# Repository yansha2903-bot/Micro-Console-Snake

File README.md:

# SnakeOnXIAO 🐍

A pocket-sized, custom-built retro gaming console made from scratch just to play the legendary Snake game!

This repository contains the full hardware design (KiCad schematic and PCB layout) and the custom C++ game engine running on a **Seeed Studio XIAO RP2040** microcontroller.

---

##  Project Structure

* **`PCB/`** — KiCad project files:
* `*.kicad_pro` — KiCad project management file.
* `*.kicad_sch` — Clean electrical schematic with custom net labels.
* `*.kicad_pcb` — Custom PCB routing, component layout, and geometric board shape.
* **`Firmware/`** — Game source code:
* `*codeSnake.ino` — Arduino IDE C++ sketch running the custom Snake game loop.
* * **`Images`** — images of my project.

---

##  Hardware & Architecture

* **Microcontroller:** Seeed Studio XIAO RP2040 (chosen for its tiny form factor and huge performance).
* **Display:** 0.96" I2C OLED display ($128 \times 64$ pixels) powered by the SSD1306 driver.
* **Controls:** 4x 6x6mm tactile buttons arranged as a classic D-Pad layout for fluid movement.
* **Pinout Configuration:**
* **Buttons (D-Pad):** Connected directly to digital pins `D0` (Up), `D1` (Down), `D2` (Left), and `D3` (Right) using internal `INPUT_PULLUP` resistors.
* **OLED Screen (I2C):** Connected to hardware I2C pins `D4` (SDA) and `D5` (SCL). Powered by the `3V3` and `GND` lines.

---

##  Game Engine Features

The game code is written in C++ using Arduino IDE and utilizes `Adafruit_GFX` and `Adafruit_SSD1306` libraries.

* **Dynamic Game Loop:** Runs at a stable frame rate, processing inputs, updating game logic, and rendering graphics in real-time.
* **Smart Collision Detection:** Full grid tracking to handle when the snake eats food (and grows!), hits the custom map borders, or runs into its own tail.
* **Grid-Aligned Spawning:** Random food spawning that perfectly matches the coordinate system of the snake segments.
* **Zero External Components:** Uses the RP2040's internal pull-up resistors to keep the PCB layout extremely clean and beginner-friendly.

---

##  How to Open and Explore

### 1. Hardware & PCB Layout (KiCad)
1. Download or clone this repository.
2. Open **KiCad 10** (or newer).
3. Load the project from the `PCB/` directory.
4. Open the Schematic Editor to view connections, or jump into the PCB Editor and hit `Alt + 3` to see the full 3D model of the console!

### 2. Flashing the Firmware (Arduino)
1. Open the `.ino` file in the **Arduino IDE**.
2. Go to *Tools -> Manage Libraries* and install **Adafruit GFX** and **Adafruit SSD1306**.
3. Select **Seeed XIAO RP2040** in your Boards Manager.
4. Connect your console via USB-C, choose the correct port, and hit **Upload**!

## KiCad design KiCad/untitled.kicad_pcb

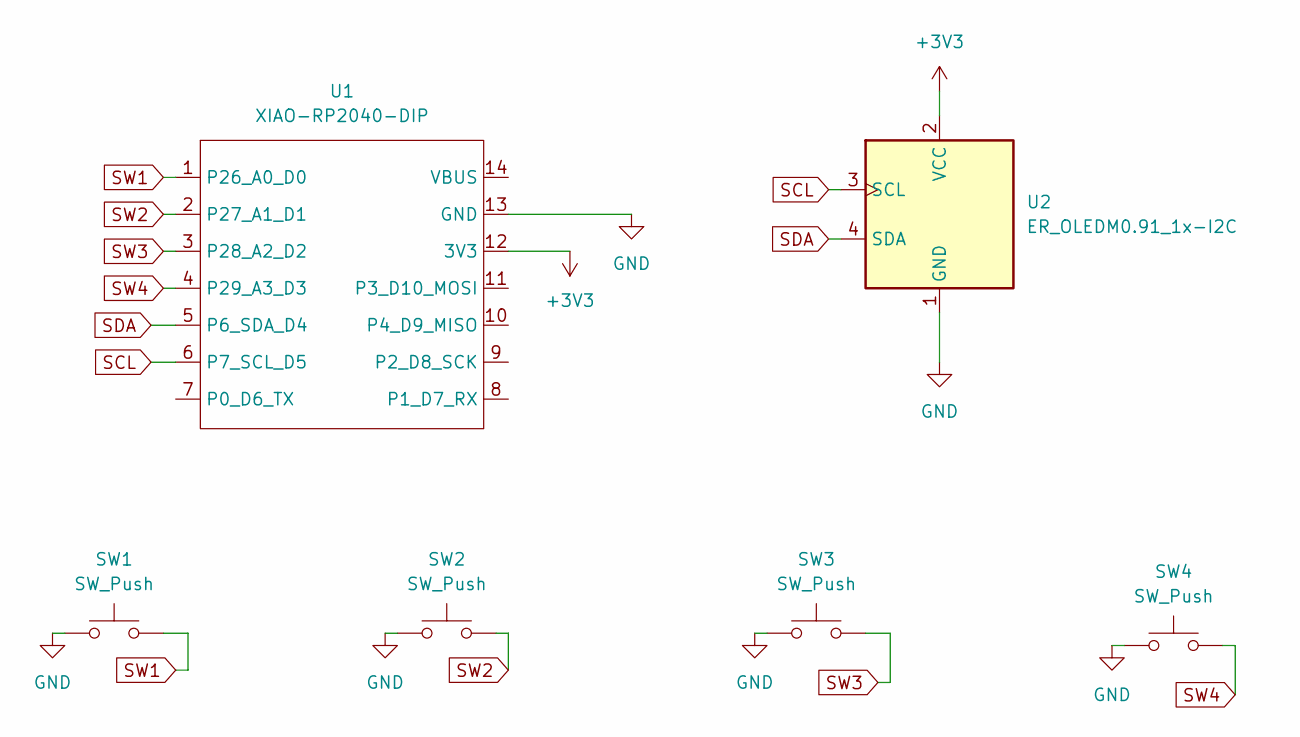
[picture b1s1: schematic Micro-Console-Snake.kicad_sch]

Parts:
SW1, SW2, SW3, SW4: SW_Push; SW_PUSH_6mm
U1: XIAO-RP2040-DIP; DIP-14_W7.62mm
U2: ER_OLEDM0.91_1x-I2C

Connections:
+3V3: U1.12 (3V3), U2.2 (VCC)
GND: SW1.1, SW2.1, SW3.1, SW4.1, U1.13 (GND), U2.1 (GND)
SCL: U1.6 (P7_SCL_D5), U2.3 (SCL)
SDA: U1.5 (P6_SDA_D4), U2.4 (SDA)
SW1: SW1.2, U1.1 (P26_A0_D0)
SW2: SW2.2, U1.2 (P27_A1_D1)
SW3: SW3.2, U1.3 (P28_A2_D2)
SW4: SW4.2, U1.4 (P29_A3_D3)

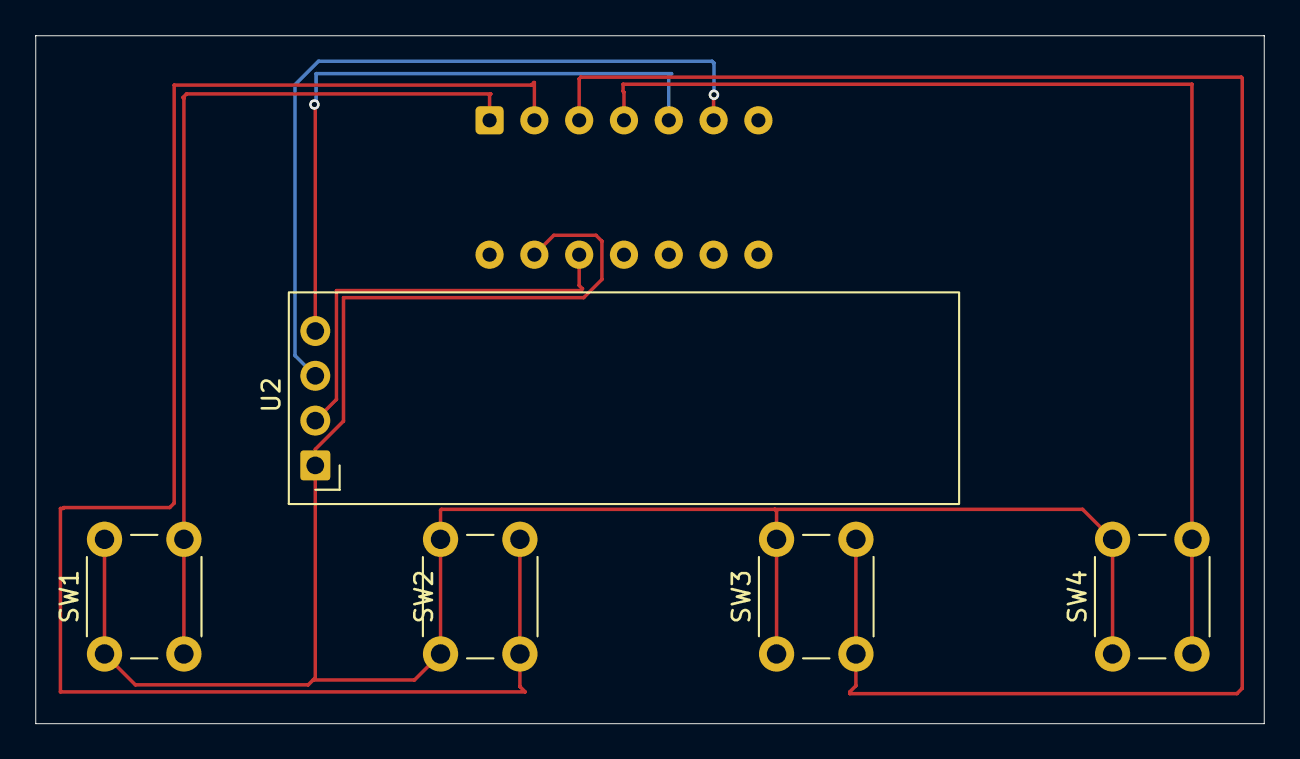
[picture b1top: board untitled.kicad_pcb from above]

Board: 2 copper layers, 69.6 x 39.0 mm, 6 parts (1 on the bottom side), 8 nets.

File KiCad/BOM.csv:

"Reference","Qty","Value","DNP","Exclude from BOM","Exclude from Board","Footprint","Datasheet"
"SW1,SW2,SW3,SW4","4","SW_Push","","","","Button_Switch_THT:SW_PUSH_6mm",""
"U1","1","XIAO-RP2040-DIP","","","","Package_DIP:DIP-14_W7.62mm",""
"U2","1","ER_OLEDM0.91_1x-I2C","","","","Display:ER_OLEDM0.91_1x-I2C","https://www.buydisplay.com/download/manual/ER-OLEDM0.91-1_Da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"
